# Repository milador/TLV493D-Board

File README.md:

# TLV493D-Board

This is a 3-axis magnetometer board based on Infineon TLV493D 3D magnetic sensor. The board provides both Qwiic/STEMMA connector and a 4 pin header which can be used to read sensor data through I2C communication protocol.

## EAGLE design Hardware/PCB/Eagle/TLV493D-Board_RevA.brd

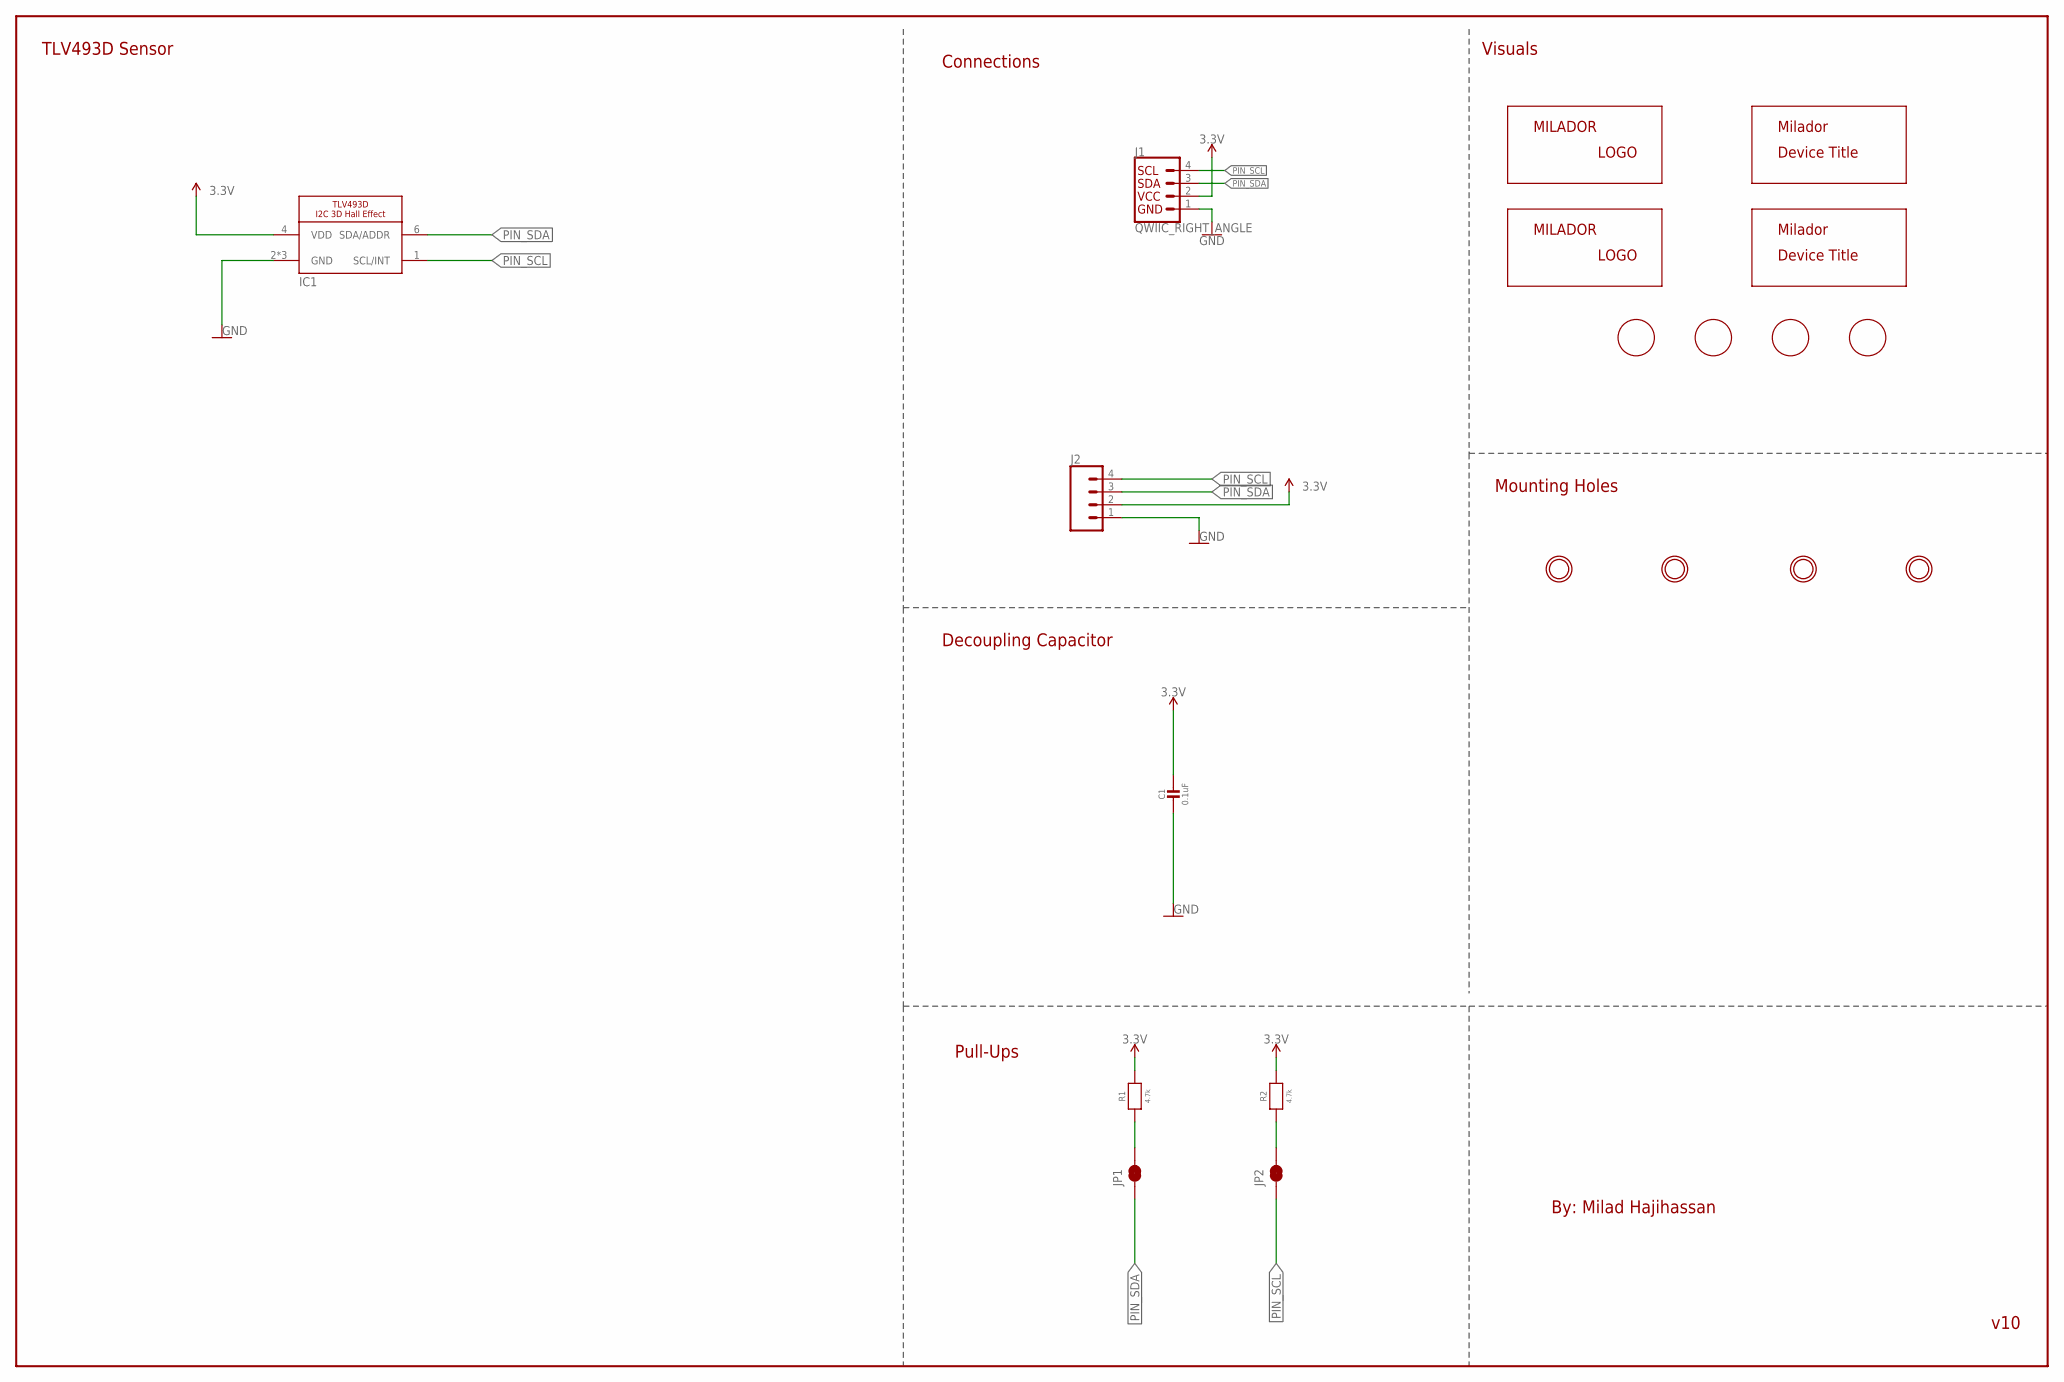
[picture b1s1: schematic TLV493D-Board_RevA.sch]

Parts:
C1: 0.1uF; 0805
IC1: TLV493D; SOT23-6
J1: QWIIC_RIGHT_ANGLE; CONNECTORS_JST04_1MM_RA
J2: CONNECTORS_CONN_041X04_NO_SILK; CONNECTORS_1X04_NO_SILK
JP1, JP2: JUMPERS-SMT_2_NC_TRACE_SILK; JUMPERS_SMT-JUMPER_2_NC_TRACE_SILK
LABEL_3V_BOTTOM: MILADOR-LABEL-3V; LABEL-3V
LABEL_GND_BOTTOM: MILADOR-LABEL-GND; LABEL-GND
LABEL_MILADOR_BOTTOM: MILADOR-LOGO-; MILADOR_LOGO1
LABEL_MILADOR_TLV493D_BOTTOM, LABEL_MILADOR_TLV493D_TOP: MILADOR-DEVICE-TLV493D_BOARD; MILADOR_TLV493D_BOARD
LABEL_MILADOR_TOP: MILADOR-LOGO-; MILADOR_LOGO1
LABE_SCL_BOTTOM: MILADOR-LABEL-SCL; LABEL-SCL
LABE_SDA_BOTTOM: MILADOR-LABEL-SDA; LABEL-SDA
M1, M2, M3, M4: MOUNTINGHOLE2.5; MOUNTINGHOLE_2.5_PLATED
R1, R2: 4.7k; 0603-NO

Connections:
3.3V: C1.1, IC1.4 (VDD), J1.2, J2.2, R1.2, R2.2
GND: C1.2, IC1.2 (GND), IC1.3 (GND), IC1.5 (GND), J1.1, J2.1
unnamed: JP1.2, R1.1
unnamed: JP2.2, R2.1
PIN_SCL: IC1.1 (SCL/INT), J1.4, J2.4, JP2.1
PIN_SDA: IC1.6 (SDA/ADDR), J1.3, J2.3, JP1.1

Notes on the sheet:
v10
Connections
By: Milad Hajihassan
Visuals
Pull-Ups
Mounting Holes
Decoupling Capacitor
TLV493D Sensor

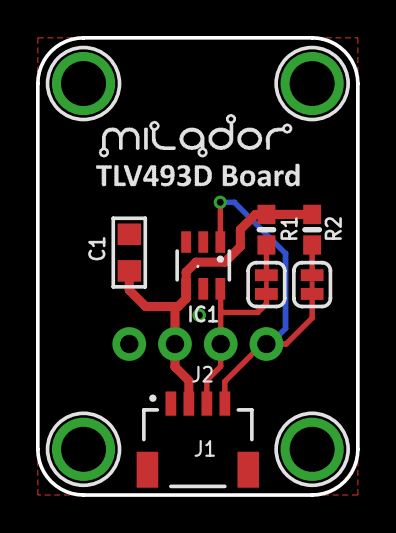
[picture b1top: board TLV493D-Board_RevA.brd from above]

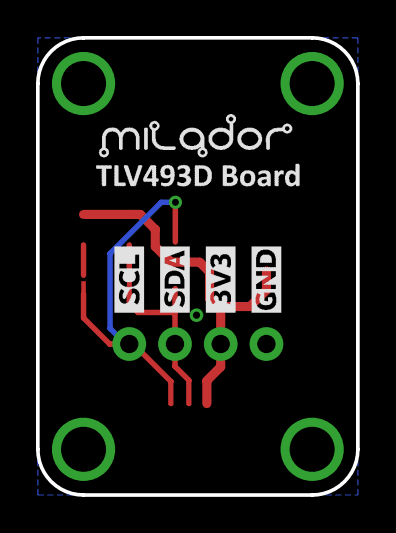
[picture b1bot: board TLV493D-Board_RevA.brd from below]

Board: 2 copper layers, 17.8 x 25.4 mm, 20 parts (6 on the bottom side), 6 nets.

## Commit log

2022-06-24 Added design files

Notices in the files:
parts and their libraries:
SparkFun-PowerSymbols: Licensing: Creative Commons ShareAlike 4.0 International - https://creativecommons.org/licenses/by-sa/4.0
